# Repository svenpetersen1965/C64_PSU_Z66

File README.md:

# C64_PSU_Z66
This is a PSU for the Commodore C64 in the Kradex Z66 case. The goal of the development is a budget but capable and reliable PSU for the C64.

This repository contains a full documenation and all project files. The <a href="https://github.com/svenpetersen1965/C64_PSU_Z66/blob/main/Rev.%201/PDF/C64PSU-Z66_Rev1.pdf">documentation</a> can be found in the pdf subdirectory. Read it, please. 

Learn more about cable making: Please visit my <a href="http://tech.guitarsite.de/cable_making.html">website</a>.

The BOM value of the PSU is 42.16€ (as of February 2022).

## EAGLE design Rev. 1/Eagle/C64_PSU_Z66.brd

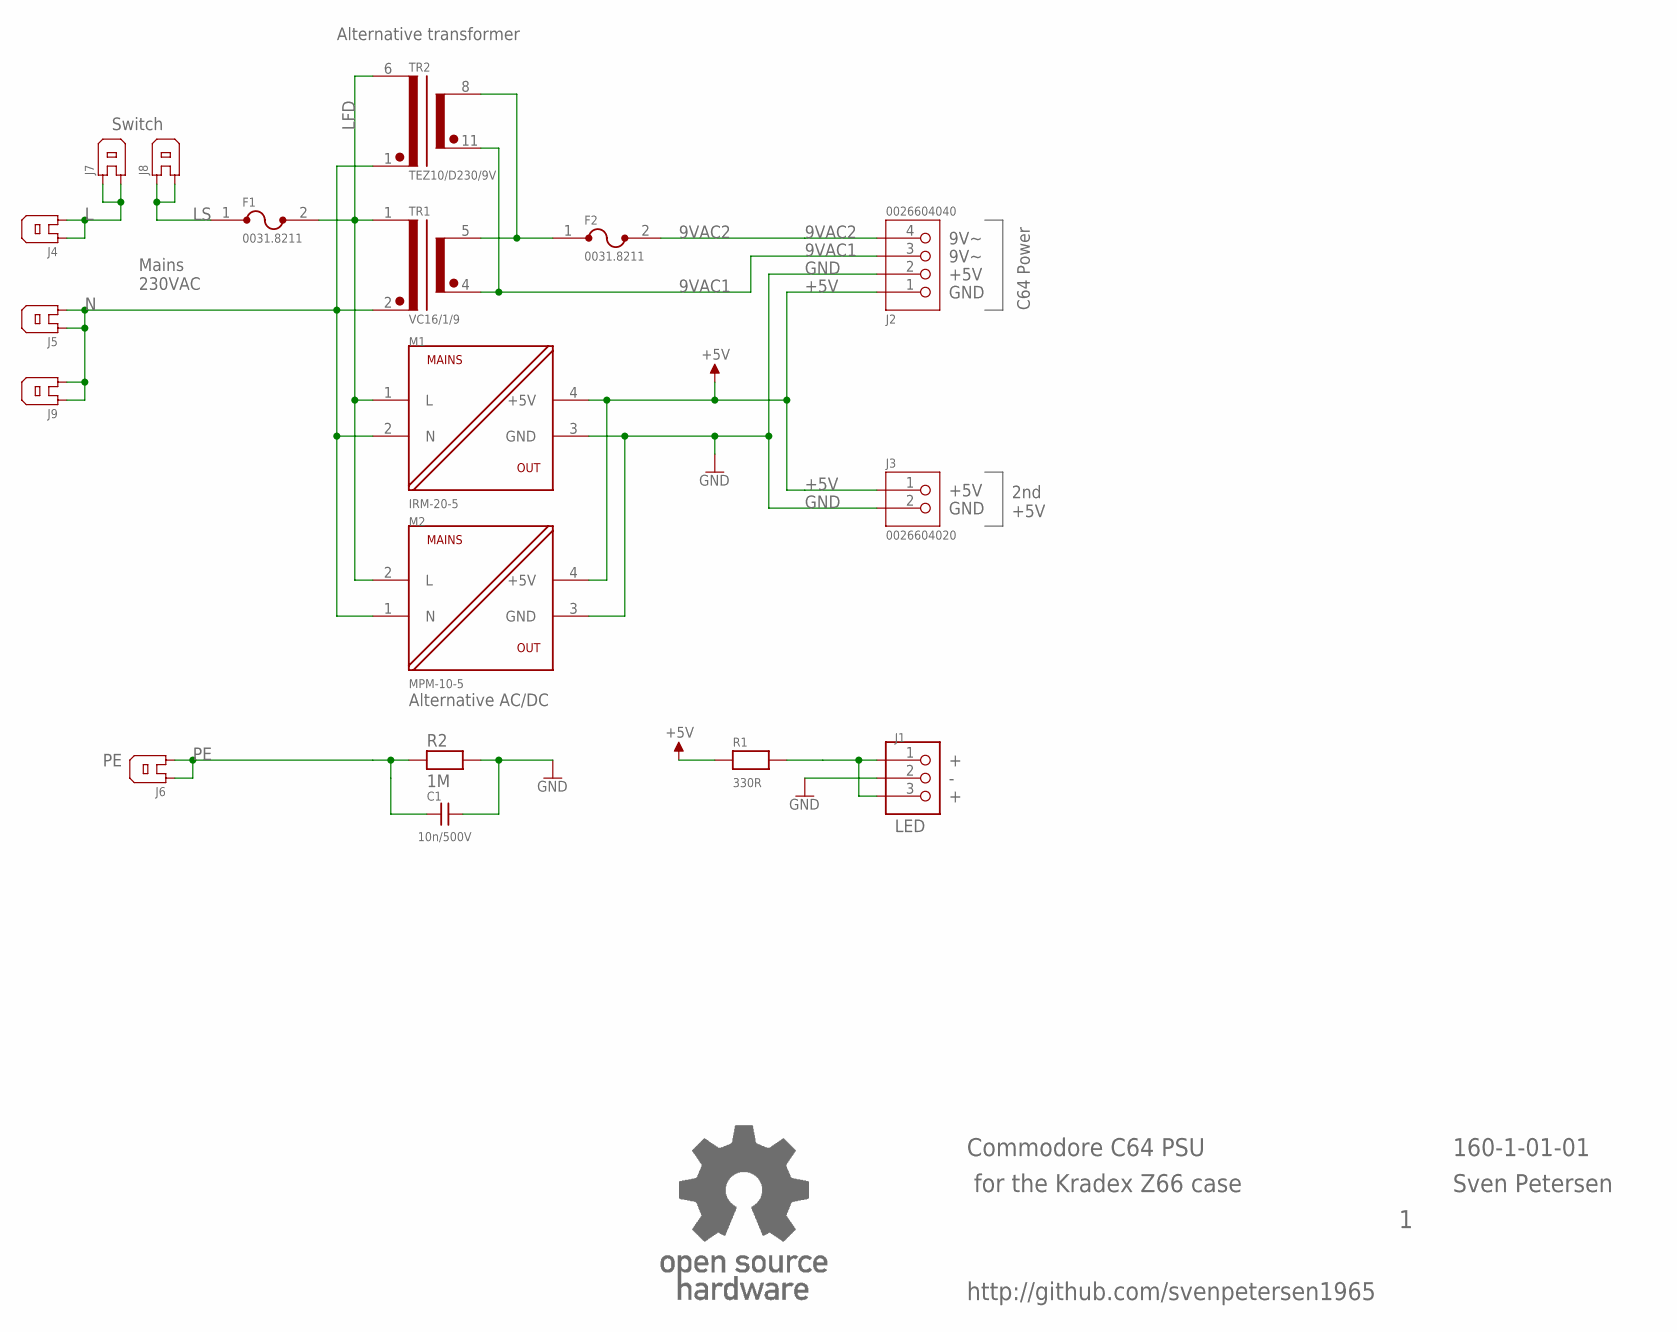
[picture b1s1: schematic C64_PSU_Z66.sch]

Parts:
C1: 10n/500V; C-5
F1, F2: 0031.8211
J1: PINHD-1X3; 1X03
J2: 0026604040; SPOX_3.96_4P
J3: 0026604020; SPOX_3.96_2P
J4, J5, J6, J7, J8, J9: FLA6,3
M1: IRM-20-5; IRM-5-20
M2: MPM-10-5; MPM10
R1: 330R; R-10
R2: 1M; R-10
TR1: VC16/1/9
TR2: TEZ10/D230/9V; TEZ10
U$8: OPEN_SOURCE_HW; OPENHW

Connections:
9VAC1: J2.3, TR1.4 (SEC12), TR2.11 (SEC12)
9VAC2: F2.2, J2.4
+5V: J2.1, J3.1, M1.4 (+5V), M2.4 (+5V), R1.1
GND: C1.2, J1.2, J2.2, J3.2, M1.3 (GND), M2.3 (GND), R2.2
L: J4.1, J4.2, J7.1, J7.2
LFD: F1.2, M1.1 (L), M2.2 (L), TR1.1 (PRI1), TR2.6 (PRI1)
LS: F1.1, J8.1, J8.2
N: J5.1, J5.2, J9.1, J9.2, M1.2 (N), M2.1 (N), TR1.2 (PRI2), TR2.1 (PRI2)
unnamed: J1.1, J1.3, R1.2
unnamed: F2.1, TR1.5 (SEC11), TR2.8 (SEC11)
PE: C1.1, J6.1, J6.2, R2.1

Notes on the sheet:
Alternative transformer
Alternative AC/DC
LED
9V~
+5V
GND
Mains 230VAC
Commodore C64 PSU
Sven Petersen
160-1-01-01
http://github.com/svenpetersen1965
for the Kradex Z66 case
C64 Power
2nd +5V
Switch

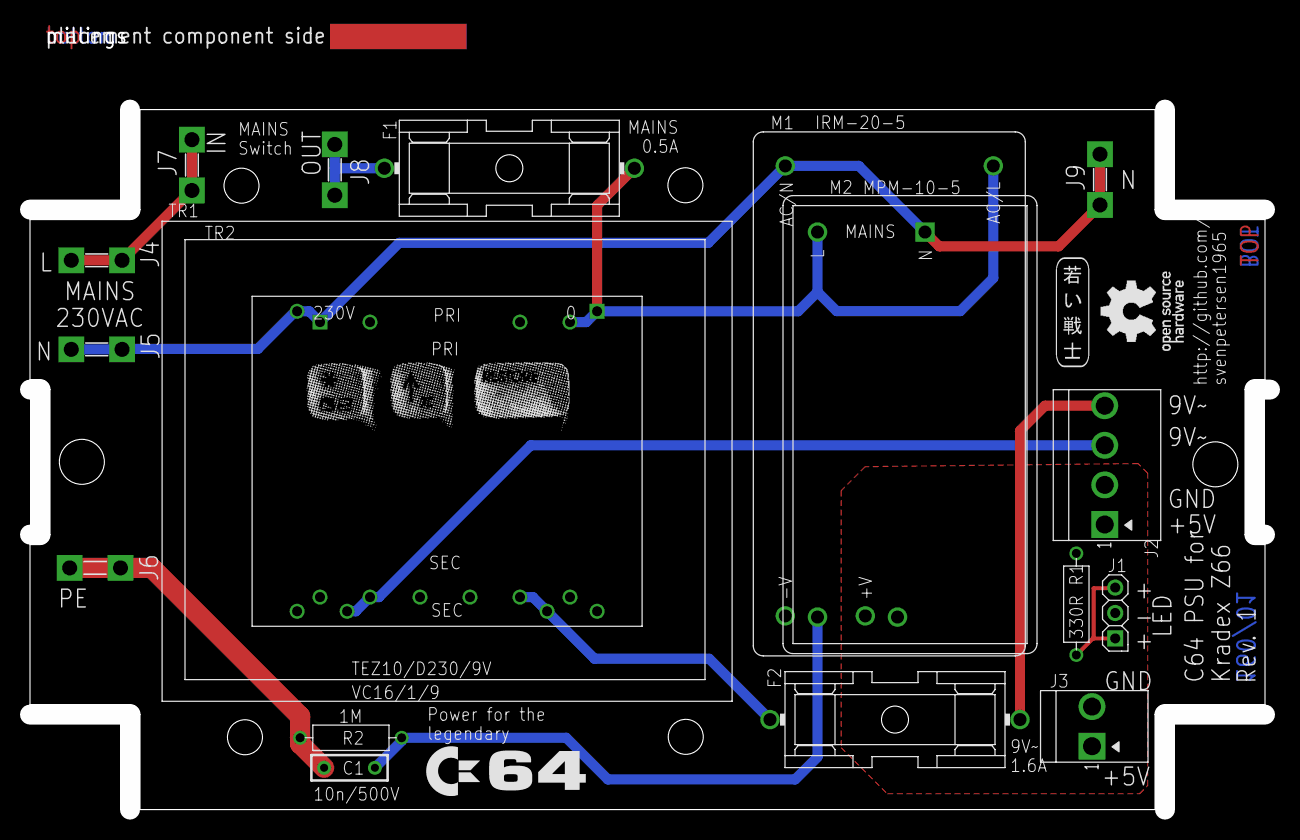
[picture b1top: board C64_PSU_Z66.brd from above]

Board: 2 copper layers, 124.0 x 78.0 mm, 25 parts (0 on the bottom side), 11 nets.

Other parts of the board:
U$7: Z66
U$9: C64_LOGO
U$10: PCB-TITLE/
U$11: 2LAYER
U$12: C64_KEYS
U$13: SVEN_TAG

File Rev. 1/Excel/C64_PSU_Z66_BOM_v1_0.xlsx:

C64 PSU "Z66" Rev. 1
Bill of Material Rev. 1.0
Pos. | Qty | Value | Footprint | Ref.-No. | Comment
1 | 1 | 160-2-01-01 | 2 Layer | PCB Rev. 1 | 2 layer, Cu 35µ, HASL, 123.5 x 70.0mm, 1.6mm FR4
2 | 6 | 6.3 x 0.8 | FLA6,3 | J4, J5, J6, J7, J8, J9 | Spade connector f. PCB, e.g. Reichelt VT FS-P 6,35
3 | 1 | Pin header 1x3, 2.54mm | 1X03 | J1 | e.g. MPE Garry 087-1-003, Reichelt MPE 087-1-003
4 | 1 | dupont housing, 3p |  | (J1) | ebay, AliExpress or other (optional: for power LED)
5 | 2 | dupont terminals, female |  | (J1) | ebay, AliExpress or other (optional: for power LED)
6 | 1 | Power LED + LED holder |  | (J1) | red, yellow, green, blue (optional)
7 | 1 | 26604020 | SPOX_3.96_2P | J3 | optional (+5V tap): Molex SPOX, e.G. Reichelt: MOLEX 26604020, tme.eu: MX-26-60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
8 | 1 | 09503021 |  | (J3) | crimp housing, optional (for +5V tap): Molex. E.g. Reichelt: MOLEX 9503021, tme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
9 | 2 | 08500106 |  | (J3) | crimp terminal, optional (for +5V tap), Molex. E.g. Reichelt: MOLEX 08500106, t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
10 | 1 | 26604040 | SPOX_3.96_4P | J2 | Molex SPOX, e.G. Reichelt: MOLEX 26604040, tme.eu: MX-26-60-4040
11 | 1 | 09503041 |  | (J2) | crimp housing: Molex. E.g. Reichelt: MOLEX 9503041, tme.eu: MX-2139-4A
12 | 4 | 08500106 |  | (J2) | crimp terminal, Molex. E.g. Reichelt: MOLEX 08500106, tme.eu: MX-2478-1-P913L (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
13 | 2 | 0031.8211 | 318211 | F1, F2 | Schurter fuse holder (5x20mm). E.g. Reichelt: PL OGN-25, tme.eu: 0031.8211
14 | 1 | 0.5A slow blow | 20x5mm | (F1) | Mains fuse
15 | 1 | 1.6A slow blow | 20x5mm | (F2) | option: Fuse for 9VAC (for VC16/1/9 transformer)
16 | 1 | 1.0A slow blow | 20x5mm | (F2) | option: Fuse for 9VAC (for TEZ10/D230/9V transformer)
17 | 1 | 10n/500V | C-5 | C1 | Ceramic Cap, 500V, pitch 5mm, Reichelt: KERKO-500 10N, tme.eu: CCH-10K (=10 pac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
18 | 1 | 1M | R-10 | R2 | Resistor, metal film, 5% or better, 0,6W
19 | 1 | 330R | R-10 | R1 | Resistor, metal film, 5% or better, 0,6W
20 | 1 | IRM-20-5 | IRM-5-20 | M1 | Mean Well. Reichelt IRM-20-5, tme.eu: IRM-20-5 (4A)
21 | 1 | MPM-10-5 | MPM10 | M2 | alternative for M1: Mean Well. Tme.eu: MPM-10-5 (2A)
22 | 1 | TEZ10/D230/9V | TEZ10 | TR2 | BREVE TUFVASSONS transformer, alternative for TR1, tme.eu: TEZ10/D/9V. Recommen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
23 | 1 | VC16/1/9 | VC16/1/9 | TR1 | alternative for TR2: BLOCK transformer, Reichelt: EI 54/18,8 109 not recommende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
24 | 10cm | AWG24/0.25mm², red |  |  | Cable for Power LED (option)
25 | 10cm | AWG24/0.25mm², black |  |  | Cable for Power LED (option)
26 | 3cm | 2.4/1.2mm |  |  | shrinkable sleve, shrink ration 1:2 (power LED)
27 | 10cm | AWG21/0.5mm², red |  |  | Cable for +5V tap (option)
28 | 10cm | AWG21/0.5mm², black |  |  | Cable for +5V tap (option)
29 | 1 | Connector (barrel jack, 5.5/2.5) |  |  | Connector for +5V tap (option), e.g. Reichelt: HEBL 25
30 | 1 | mains cable, 3x0.75mm² |  |  | Mains cable (3 wire recommended), AWG 20
31 | 1 | MAS 70S |  |  | Hirschmann DIN plug 7pin, 262°. Reichelt: MAS 70S, tme.eu: MAS70SGR. Example fo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
32 | 0.5m | 4x0.5mm² |  | (J2) | Cable for output voltages. 4xAWG21
33 | 6 | 2-520184-2 |  | (J4), (J5), (J6), (J7), (J8), (J9) | TE connectivity, tme.eu: 2-520184-2 or Reichelt RND 465-00067. Example for 6.3 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
34 | 3 | FastOn connector 4.8x0.8, red, fully isolated |  |  | FastOn for power switch
34 | 30cm | AWG20/0.75mm², black |  |  | Cable for Power Switch
35 | 1 | 1858.1103 |  |  | option for rectangular Power switch: Marquardt 1858.1103, Reichelt: WIPPE 1858.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
36 | 1 | R13112BBR3 |  |  | Recommended Power switch (round, 20mm): Bulgin, tme.eu: AE-R13112BNAA, Reichelt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
37 | 1 | Kradex Z66 |  |  | Kradex Case, tme.eu. Black: Z66-ABS, Grey: Z66J-ABS
38 | 4 | screws C2.9x6.5mm |  |  | self tapping screws, e.g. DIN 7981
39 | 2 | small cable ties |  |  | e.g. 102x2.5mm (Reichelt KAB 100-2,5)

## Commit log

2022-02-18 Initial upload
